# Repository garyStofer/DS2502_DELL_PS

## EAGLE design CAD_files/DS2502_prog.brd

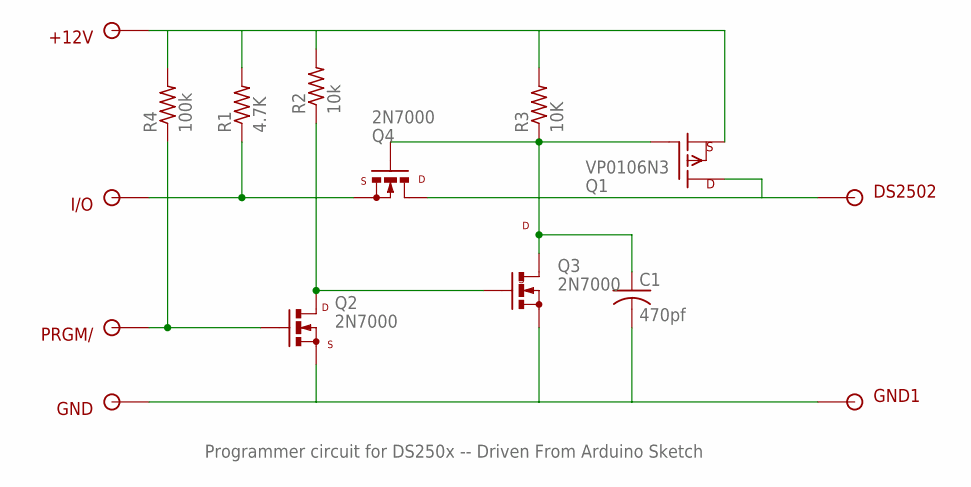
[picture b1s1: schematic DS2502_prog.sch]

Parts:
+12V: SOLDER_POINTA; P1-13
C1: 470pf; C025-025X050
DS2502: SOLDER_POINTA; P1-13
GND, GND1: SOLDER_POINTA; P1-13
I/O: SOLDER_POINTA; P1-13
PRGM/: SOLDER_POINTA; P1-13
Q1: VP0106N3; TO92-
Q2, Q3, Q4: 2N7000; TO92-LINE
R1: 4.7K; 0207/2V
R2: 10k; 0309/10
R3: 10K; 0207/2V
R4: 100k; 0309/10

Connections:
unnamed: +12V.1, Q1.3 (S), R1.2, R2.2, R3.2, R4.2
unnamed: I/O.1, Q4.3 (S), R1.1
unnamed: Q2.1 (D), Q3.2 (G), R2.1
unnamed: PRGM/.1, Q2.2 (G), R4.1
unnamed: C1.2, GND.1, GND1.1, Q2.3 (S), Q3.3 (S)
unnamed: C1.1, Q1.2 (G), Q3.1 (D), Q4.2 (G), R3.1
unnamed: DS2502.1, Q1.1 (D), Q4.1 (D)

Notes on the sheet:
Programmer circuit for DS250x -- Driven From Arduino Sketch

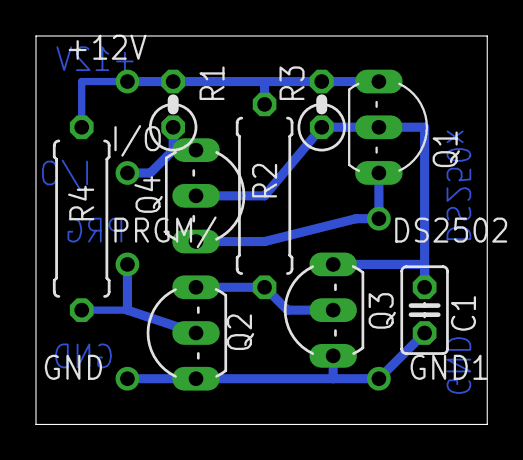
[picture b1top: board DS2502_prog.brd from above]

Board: 2 copper layers, 25.1 x 21.6 mm, 15 parts (0 on the bottom side), 7 nets.

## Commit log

2015-09-15 Initial
2015-09-15 typos fixed
2015-09-18 Added CAD files and included link to PCB from OSH
2017-09-23 removed eagle.eps file added gitignore
2018-10-30 added #defines for pins and change so that it connects to an Arduino on a Air_LCD board -- Enabled a LED for display while programming
2018-10-30 added OneWire library local to project
2018-10-30 added captured response trace from Onewire device
2023-02-28 Added defines for pins used to control circuit added define to not program -- only read added better printout for read data and device ID changed serial connection speed to the standard 115200 bd
2023-03-01 fixed warning about const char *
